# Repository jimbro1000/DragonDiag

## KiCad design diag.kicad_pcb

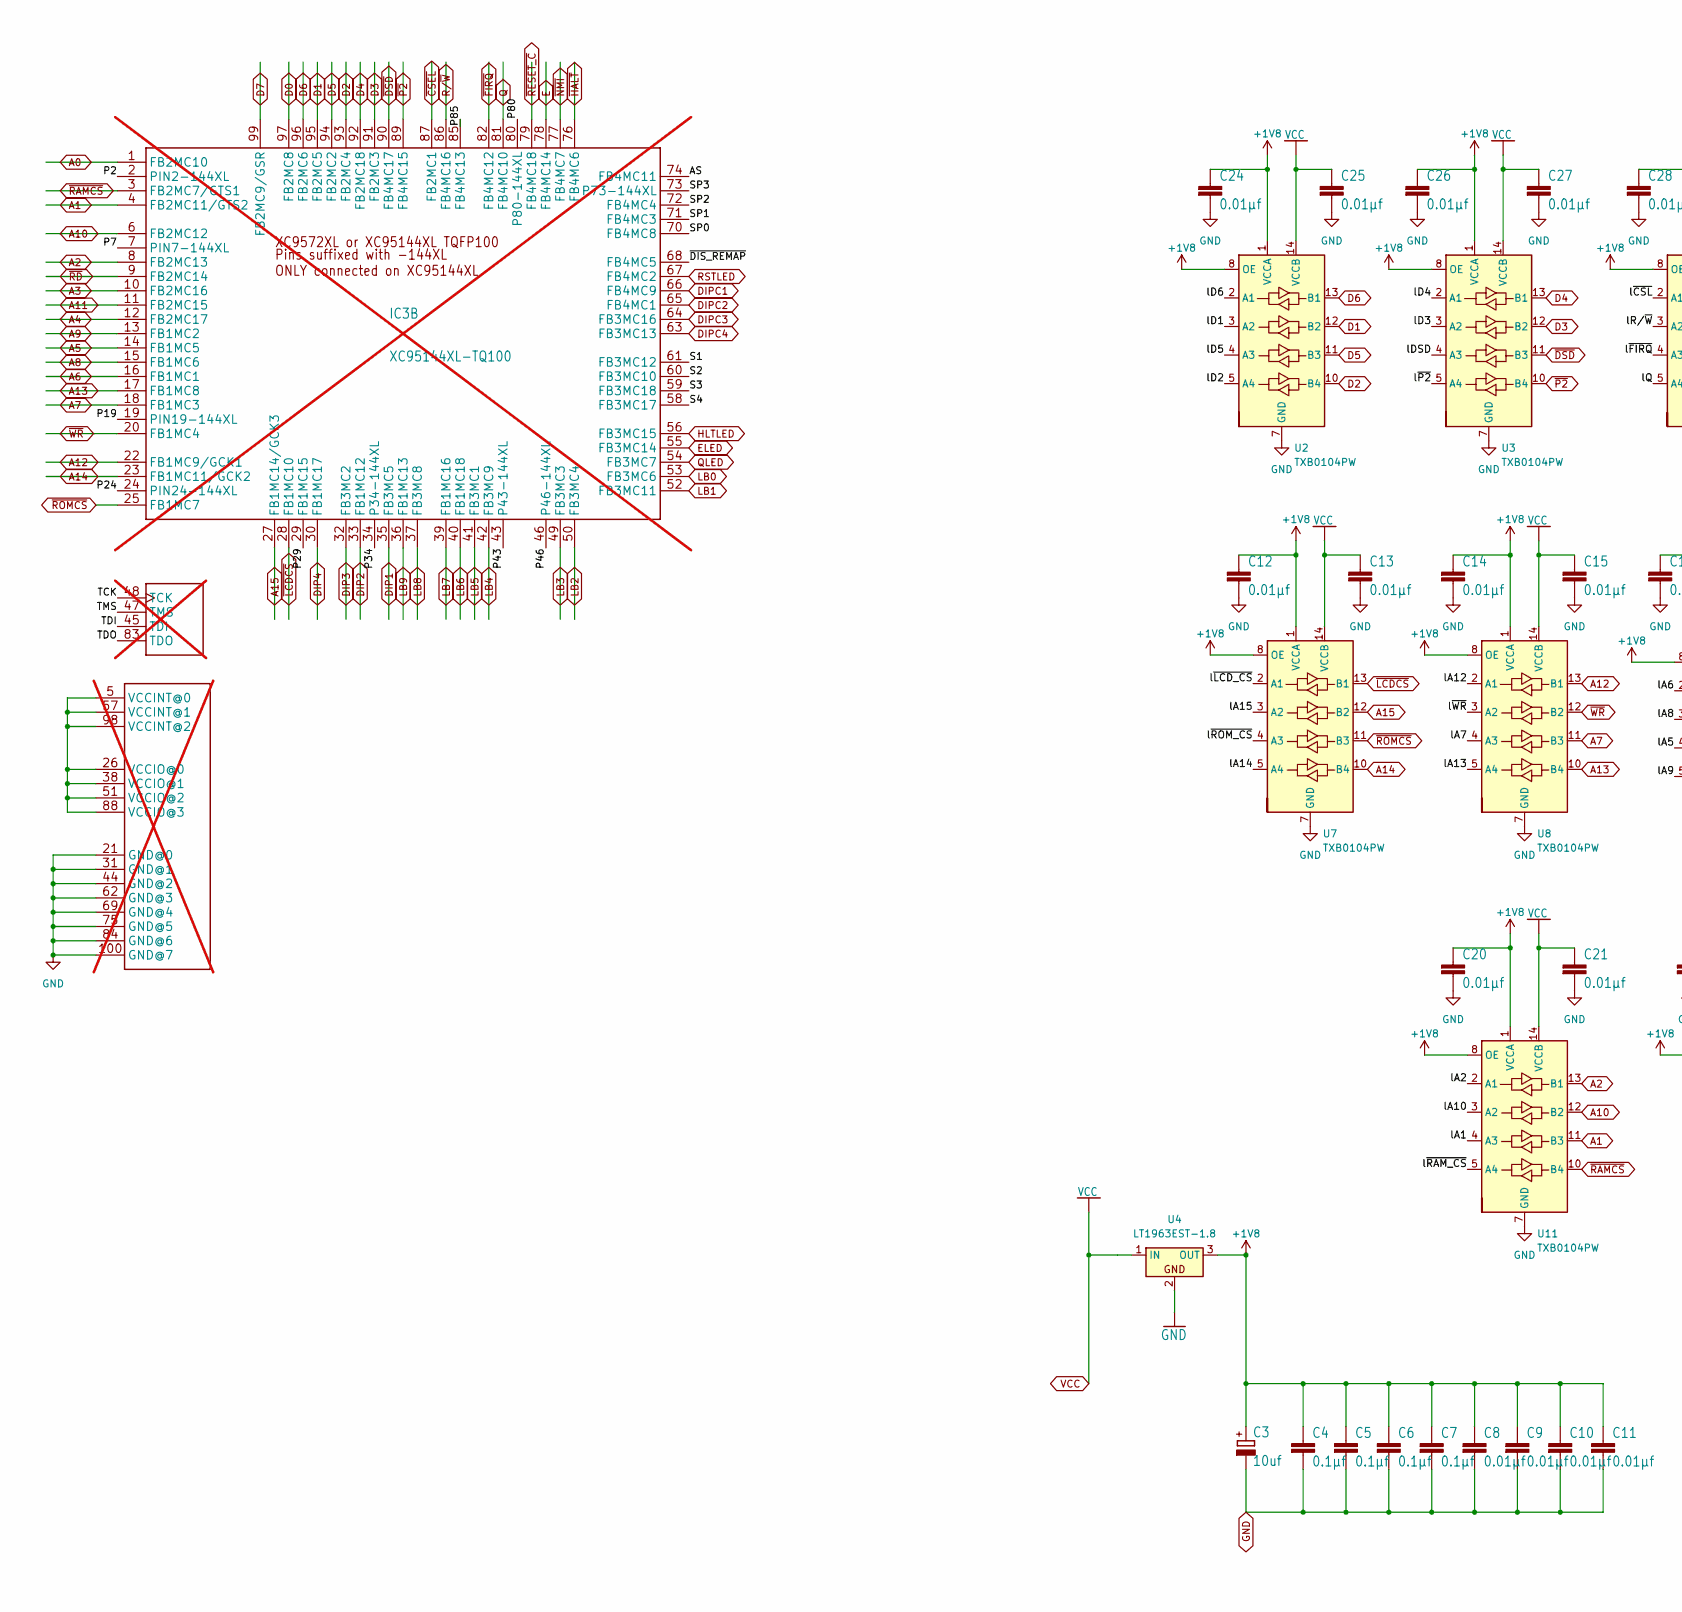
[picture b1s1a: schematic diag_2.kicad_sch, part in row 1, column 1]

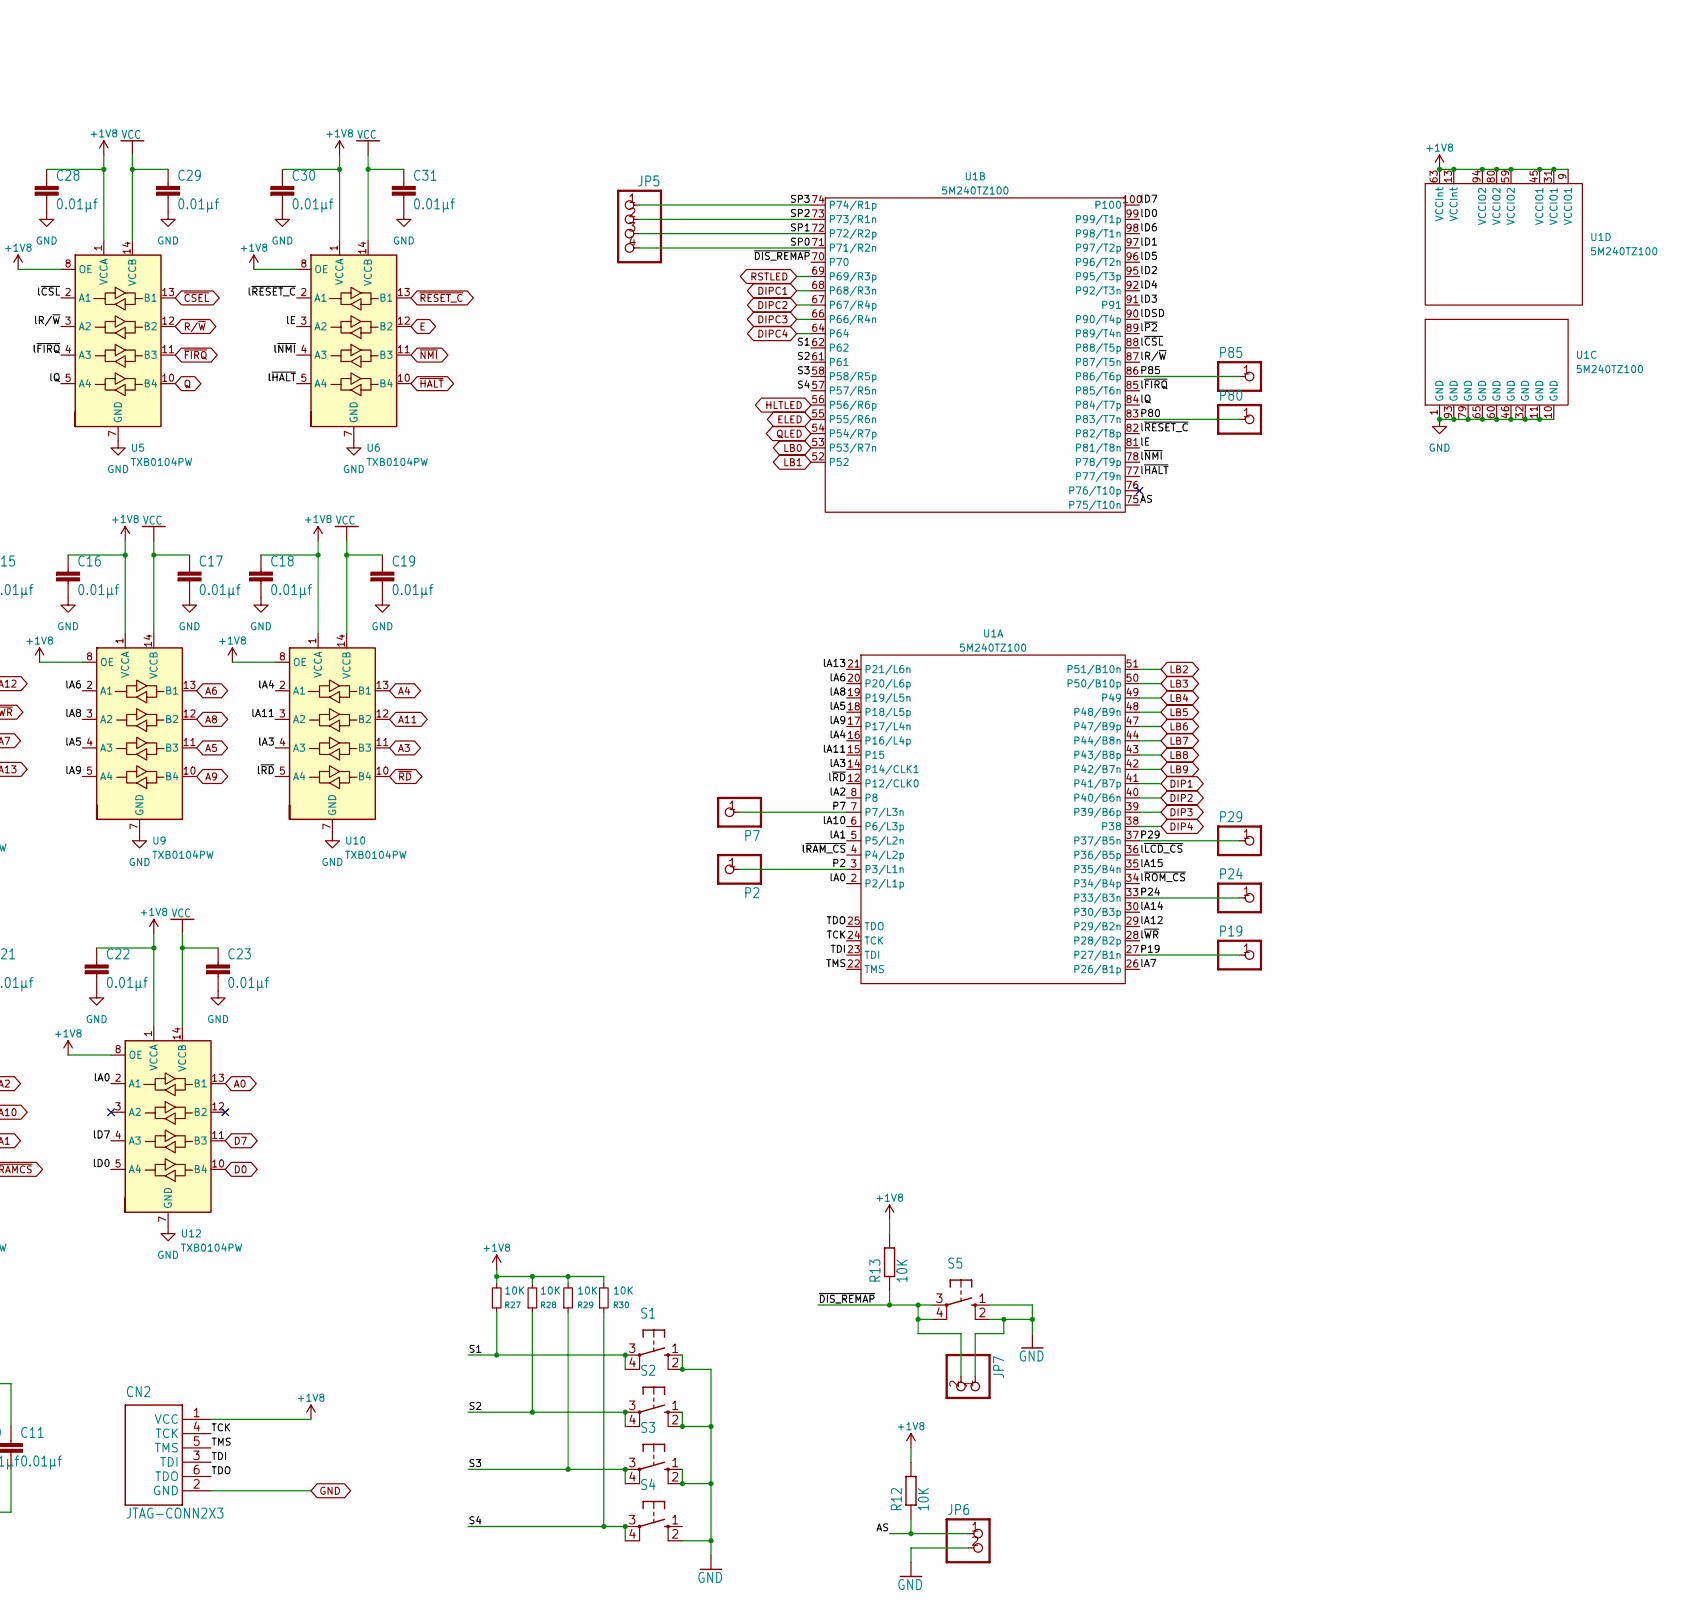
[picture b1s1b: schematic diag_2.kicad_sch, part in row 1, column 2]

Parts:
C3: 10uf; TT2D7
C4, C5, C6, C7: 0.1µf; C_0603_1608Metric
C8, C9, C10, C11, C12, C13, C14, C15, C16, C17, C18, C19, C20, C21, C22, C23, C24, C25, C26, C27, C28, C29, C30, C31: 0.01µf; C_0603_1608Metric
CN2: JTAG-CONN2X3; 2X3
IC3: XC95144XL-TQ100; TQ100; not fitted
JP5: PINHD-1X4; 1X04
JP6, JP7: PINHD-1X2; 1X02
P2, P7, P19, P24, P29, P80, P85: PINHD-1X1; 1X01
R12, R13, R27, R28, R29, R30: 10K; R_0805_2012Metric
S1, S2, S3, S4, S5: 10-XX; B3F-10XX
U1: 5M240TZ100; TQFP-100_14x14mm_P0.5mm
U2, U3, U5, U6, U7, U8, U9, U10, U11, U12: TXB0104PW; TSSOP-14_4.4x5mm_P0.65mm
U4: LT1963EST-1.8; SOT-223-3_TabPin2

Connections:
+1V8: C3.+, C4.1, C5.1, C6.1, C7.1, C8.1, C9.1, C10.1, C11.1, C12.1, C14.1, C16.1, C18.1, C20.1, C22.1, C24.1, C26.1, C28.1, C30.1, CN2.1 (VCC), R12.2, R13.2, R27.2, R28.2, R29.2, R30.2, U1.9 (VCCIO1), U1.13 (VCCInt), U1.31 (VCCIO1), U1.45 (VCCIO1), U1.59 (VCCIO2), U1.63 (VCCInt), U1.80 (VCCIO2), U1.94 (VCCIO2), U2.1 (VCCA), U2.8 (OE), U3.1 (VCCA), U3.8 (OE), U4.3 (OUT), U5.1 (VCCA), U5.8 (OE), U6.1 (VCCA), U6.8 (OE), U7.1 (VCCA), U7.8 (OE), U8.1 (VCCA), U8.8 (OE), U9.1 (VCCA), U9.8 (OE), U10.1 (VCCA), U10.8 (OE), U11.1 (VCCA), U11.8 (OE), U12.1 (VCCA), U12.8 (OE); also elsewhere on the board
/diag_2/AS: IC3.74 (FB4MC11), JP6.1, R12.1, U1.75 (P75/T10n)
/diag_2/P2: IC3.2 (PIN2-144XL), P2.1, U1.3 (P3/L1n)
/diag_2/P7: IC3.7 (PIN7-144XL), P7.1, U1.7 (P7/L3n)
/diag_2/P19: IC3.19 (PIN19-144XL), P19.1, U1.27 (P27/B1n)
/diag_2/P24: IC3.24 (PIN24-144XL), P24.1, U1.33 (P33/B3n)
/diag_2/P29: IC3.29 (FB1MC15), P29.1, U1.37 (P37/B5n)
/diag_2/P80: IC3.80 (P80-144XL), P80.1, U1.83 (P83/T7n)
/diag_2/P85: IC3.85 (FB4MC13), P85.1, U1.86 (P86/T6p)
/diag_2/S1: IC3.61 (FB3MC12), R27.1, S1.3, S1.4 (P1), U1.62
/diag_2/S2: IC3.60 (FB3MC10), R28.1, S2.3, S2.4 (P1), U1.61
/diag_2/S3: IC3.59 (FB3MC18), R29.1, S3.3, S3.4 (P1), U1.58 (P58/R5p)
/diag_2/S4: IC3.58 (FB3MC17), R30.1, S4.3, S4.4 (P1), U1.57 (P57/R5n)
/diag_2/SP0: IC3.70 (FB4MC8), JP5.4, U1.71 (P71/R2n)
/diag_2/SP1: IC3.71 (FB4MC3), JP5.3, U1.72 (P72/R2p)
/diag_2/SP2: IC3.72 (FB4MC4), JP5.2, U1.73 (P73/R1n)
/diag_2/SP3: IC3.73 (P73-144XL), JP5.1, U1.74 (P74/R1p)
/diag_2/TCK: CN2.4 (TCK), IC3.48 (TCK), U1.24 (TCK)
/diag_2/TDI: CN2.3 (TDI), IC3.45 (TDI), U1.23 (TDI)
/diag_2/TDO: CN2.6 (TDO), IC3.83 (TDO), U1.25 (TDO)
/diag_2/TMS: CN2.5 (TMS), IC3.47 (TMS), U1.22 (TMS)
/diag_2/lA0: U1.2 (P2/L1p), U12.2 (A1)
/diag_2/lA1: U1.5 (P5/L2n), U11.4 (A3)
/diag_2/lA2: U1.8, U11.2 (A1)
/diag_2/lA3: U1.14 (P14/CLK1), U10.4 (A3)
/diag_2/lA4: U1.16 (P16/L4p), U10.2 (A1)
/diag_2/lA5: U1.18 (P18/L5p), U9.4 (A3)
/diag_2/lA6: U1.20 (P20/L6p), U9.2 (A1)
/diag_2/lA7: U1.26 (P26/B1p), U8.4 (A3)
/diag_2/lA8: U1.19 (P19/L5n), U9.3 (A2)
/diag_2/lA9: U1.17 (P17/L4n), U9.5 (A4)
/diag_2/lA10: U1.6 (P6/L3p), U11.3 (A2)
/diag_2/lA11: U1.15, U10.3 (A2)
/diag_2/lA12: U1.29 (P29/B2n), U8.2 (A1)
/diag_2/lA13: U1.21 (P21/L6n), U8.5 (A4)
/diag_2/lA14: U1.30 (P30/B3p), U7.5 (A4)
/diag_2/lA15: U1.35 (P35/B4n), U7.3 (A2)
/diag_2/lD0: U1.99 (P99/T1p), U12.5 (A4)
/diag_2/lD1: U1.97 (P97/T2p), U2.3 (A2)
/diag_2/lD2: U1.95 (P95/T3p), U2.5 (A4)
/diag_2/lD3: U1.91, U3.3 (A2)
/diag_2/lD4: U1.92 (P92/T3n), U3.2 (A1)
/diag_2/lD5: U1.96 (P96/T2n), U2.4 (A3)
/diag_2/lD6: U1.98 (P98/T1n), U2.2 (A1)
/diag_2/lD7: U1.100, U12.4 (A3)
/diag_2/lDSD: U1.90 (P90/T4p), U3.4 (A3)
/diag_2/lE: U1.81 (P81/T8n), U6.3 (A2)
/diag_2/lQ: U1.84 (P84/T7p), U5.5 (A4)
/diag_2/lR/~W: U1.87 (P87/T5n), U5.3 (A2)
/diag_2/l~CSL: U1.88 (P88/T5p), U5.2 (A1)
/diag_2/l~FIRQ: U1.85 (P85/T6n), U5.4 (A3)
/diag_2/l~HALT: U1.77 (P77/T9n), U6.5 (A4)
/diag_2/l~LCD_CS: U1.36 (P36/B5p), U7.2 (A1)
/diag_2/l~NMI: U1.78 (P78/T9p), U6.4 (A3)
/diag_2/l~P2: U1.89 (P89/T4n), U3.5 (A4)
/diag_2/l~RAM_CS: U1.4 (P4/L2p), U11.5 (A4)
/diag_2/l~RD: U1.12 (P12/CLK0), U10.5 (A4)
/diag_2/l~RESET_C: U1.82 (P82/T8p), U6.2 (A1)
/diag_2/l~ROM_CS: U1.34 (P34/B4p), U7.4 (A3)
/diag_2/l~WR: U1.28 (P28/B2p), U8.3 (A2)
/diag_2/~DIS_REMAP: IC3.68 (FB4MC5), JP7.2, R13.1, S5.3, S5.4 (P1), U1.70
A0: IC3.1 (FB2MC10), U12.13 (B1); also elsewhere on the board
A1: IC3.4 (FB2MC11/GTS2), U11.11 (B3); also elsewhere on the board
A2: IC3.8 (FB2MC13), U11.13 (B1); also elsewhere on the board
A3: IC3.10 (FB2MC16), U10.11 (B3); also elsewhere on the board
A4: IC3.12 (FB2MC17), U10.13 (B1); also elsewhere on the board
A5: IC3.14 (FB1MC5), U9.11 (B3); also elsewhere on the board
A6: IC3.16 (FB1MC1), U9.13 (B1); also elsewhere on the board
A7: IC3.18 (FB1MC3), U8.11 (B3); also elsewhere on the board
A8: IC3.15 (FB1MC6), U9.12 (B2); also elsewhere on the board
A9: IC3.13 (FB1MC2), U9.10 (B4); also elsewhere on the board
A10: IC3.6 (FB2MC12), U11.12 (B2); also elsewhere on the board
A11: IC3.11 (FB2MC15), U10.12 (B2); also elsewhere on the board
A12: IC3.22 (FB1MC9/GCK1), U8.13 (B1); also elsewhere on the board
A13: IC3.17 (FB1MC8), U8.10 (B4); also elsewhere on the board
A14: IC3.23 (FB1MC11/GCK2), U7.10 (B4); also elsewhere on the board
A15: IC3.27 (FB1MC14/GCK3), U7.12 (B2); also elsewhere on the board
D0: IC3.97 (FB2MC8), U12.10 (B4); also elsewhere on the board
D1: IC3.95 (FB2MC5), U2.12 (B2); also elsewhere on the board
D2: IC3.93 (FB2MC4), U2.10 (B4); also elsewhere on the board
D3: IC3.91 (FB2MC3), U3.12 (B2); also elsewhere on the board
D4: IC3.92 (FB2MC18), U3.13 (B1); also elsewhere on the board
D5: IC3.94 (FB2MC2), U2.11 (B3); also elsewhere on the board
D6: IC3.96 (FB2MC6), U2.13 (B1); also elsewhere on the board
D7: IC3.99 (FB2MC9/GSR), U12.11 (B3); also elsewhere on the board
DIP1: IC3.35 (FB3MC5), U1.41 (P41/B7p); also elsewhere on the board
DIP2: IC3.33 (FB1MC12), U1.40 (P40/B6n); also elsewhere on the board
DIP3: IC3.32 (FB3MC2), U1.39 (P39/B6p); also elsewhere on the board
DIP4: IC3.30 (FB1MC17), U1.38; also elsewhere on the board
DIPC1: IC3.66 (FB4MC9), U1.68 (P68/R3n); also elsewhere on the board
DIPC2: IC3.65 (FB4MC1), U1.67 (P67/R4p); also elsewhere on the board
DIPC3: IC3.64 (FB3MC16), U1.66 (P66/R4n); also elsewhere on the board
DIPC4: IC3.63 (FB3MC13), U1.64; also elsewhere on the board
E: IC3.78 (FB4MC14), U6.12 (B2); also elsewhere on the board
ELED: IC3.55 (FB3MC14), U1.55 (P55/R6n); also elsewhere on the board
GND: C3.-, C4.2, C5.2, C6.2, C7.2, C8.2, C9.2, C10.2, C11.2, C12.2, C13.2, C14.2, C15.2, C16.2, C17.2, C18.2, C19.2, C20.2, C21.2, C22.2, C23.2, C24.2, C25.2, C26.2, C27.2, C28.2, C29.2, C30.2, C31.2, CN2.2 (GND), IC3.21 (GND@0), IC3.31 (GND@1), IC3.44 (GND@2), IC3.62 (GND@3), IC3.69 (GND@4), IC3.75 (GND@5), IC3.84 (GND@6), IC3.100 (GND@7), JP6.2, JP7.1, S1.1 (S), S1.2 (S1), S2.1 (S), S2.2 (S1), S3.1 (S), S3.2 (S1), S4.2 (S1), S5.1 (S), S5.2 (S1), U1.1 (GND), U1.10 (GND), U1.11 (GND), U1.32 (GND), U1.46 (GND), U1.60 (GND), U1.65 (GND), U1.79 (GND), U1.93 (GND), U2.7 (GND), U3.7 (GND), U4.2, U5.7 (GND), U6.7 (GND), U7.7 (GND), U8.7 (GND), U9.7 (GND), U10.7 (GND), U11.7 (GND), U12.7 (GND); also elsewhere on the board
HLTLED: IC3.56 (FB3MC15), U1.56 (P56/R6p); also elsewhere on the board
LB0: IC3.53 (FB3MC6), U1.53 (P53/R7n); also elsewhere on the board
LB1: IC3.52 (FB3MC11), U1.52; also elsewhere on the board
LB2: IC3.50 (FB3MC4), U1.51 (P51/B10n); also elsewhere on the board
LB3: IC3.49 (FB3MC3), U1.50 (P50/B10p); also elsewhere on the board
LB4: IC3.42 (FB3MC9), U1.49; also elsewhere on the board
LB5: IC3.41 (FB3MC1), U1.48 (P48/B9n); also elsewhere on the board
LB6: IC3.40 (FB1MC18), U1.47 (P47/B9p); also elsewhere on the board
LB7: IC3.39 (FB1MC16), U1.44 (P44/B8n); also elsewhere on the board
LB8: IC3.37 (FB3MC8), U1.43 (P43/B8p); also elsewhere on the board
LB9: IC3.36 (FB1MC13), U1.42 (P42/B7n); also elsewhere on the board
unnamed: IC3.5 (VCCINT@0), IC3.26 (VCCIO@0), IC3.38 (VCCIO@1), IC3.51 (VCCIO@2), IC3.57 (VCCINT@1), IC3.88 (VCCIO@3), IC3.98 (VCCINT@2)
Q: IC3.81 (FB4MC10), U5.10 (B4); also elsewhere on the board
QLED: IC3.54 (FB3MC7), U1.54 (P54/R7p); also elsewhere on the board
RSTLED: IC3.67 (FB4MC2), U1.69 (P69/R3p); also elsewhere on the board
R/~W: IC3.86 (FB4MC16), U5.12 (B2); also elsewhere on the board
VCC: C13.1, C15.1, C17.1, C19.1, C21.1, C23.1, C25.1, C27.1, C29.1, C31.1, U2.14 (VCCB), U3.14 (VCCB), U4.1 (IN), U5.14 (VCCB), U6.14 (VCCB), U7.14 (VCCB), U8.14 (VCCB), U9.14 (VCCB), U10.14 (VCCB), U11.14 (VCCB), U12.14 (VCCB); also elsewhere on the board
~CSEL: IC3.87 (FB2MC1), U5.13 (B1); also elsewhere on the board
~DSD: IC3.90 (FB4MC17), U3.11 (B3); also elsewhere on the board
~FIRQ: IC3.82 (FB4MC12), U5.11 (B3); also elsewhere on the board
~HALT: IC3.76 (FB4MC6), U6.10 (B4); also elsewhere on the board
~LCDCS: IC3.28 (FB1MC10), U7.13 (B1); also elsewhere on the board
~NMI: IC3.77 (FB4MC7), U6.11 (B3); also elsewhere on the board
~P2: IC3.89 (FB4MC15), U3.10 (B4); also elsewhere on the board
~RAMCS: IC3.3 (FB2MC7/GTS1), U11.10 (B4); also elsewhere on the board
~RD: IC3.9 (FB2MC14), U10.10 (B4); also elsewhere on the board
~RESET_C: IC3.79 (FB4MC18), U6.13 (B1); also elsewhere on the board
~ROMCS: IC3.25 (FB1MC7), U7.11 (B3); also elsewhere on the board
~WR: IC3.20 (FB1MC4), U8.12 (B2); also elsewhere on the board

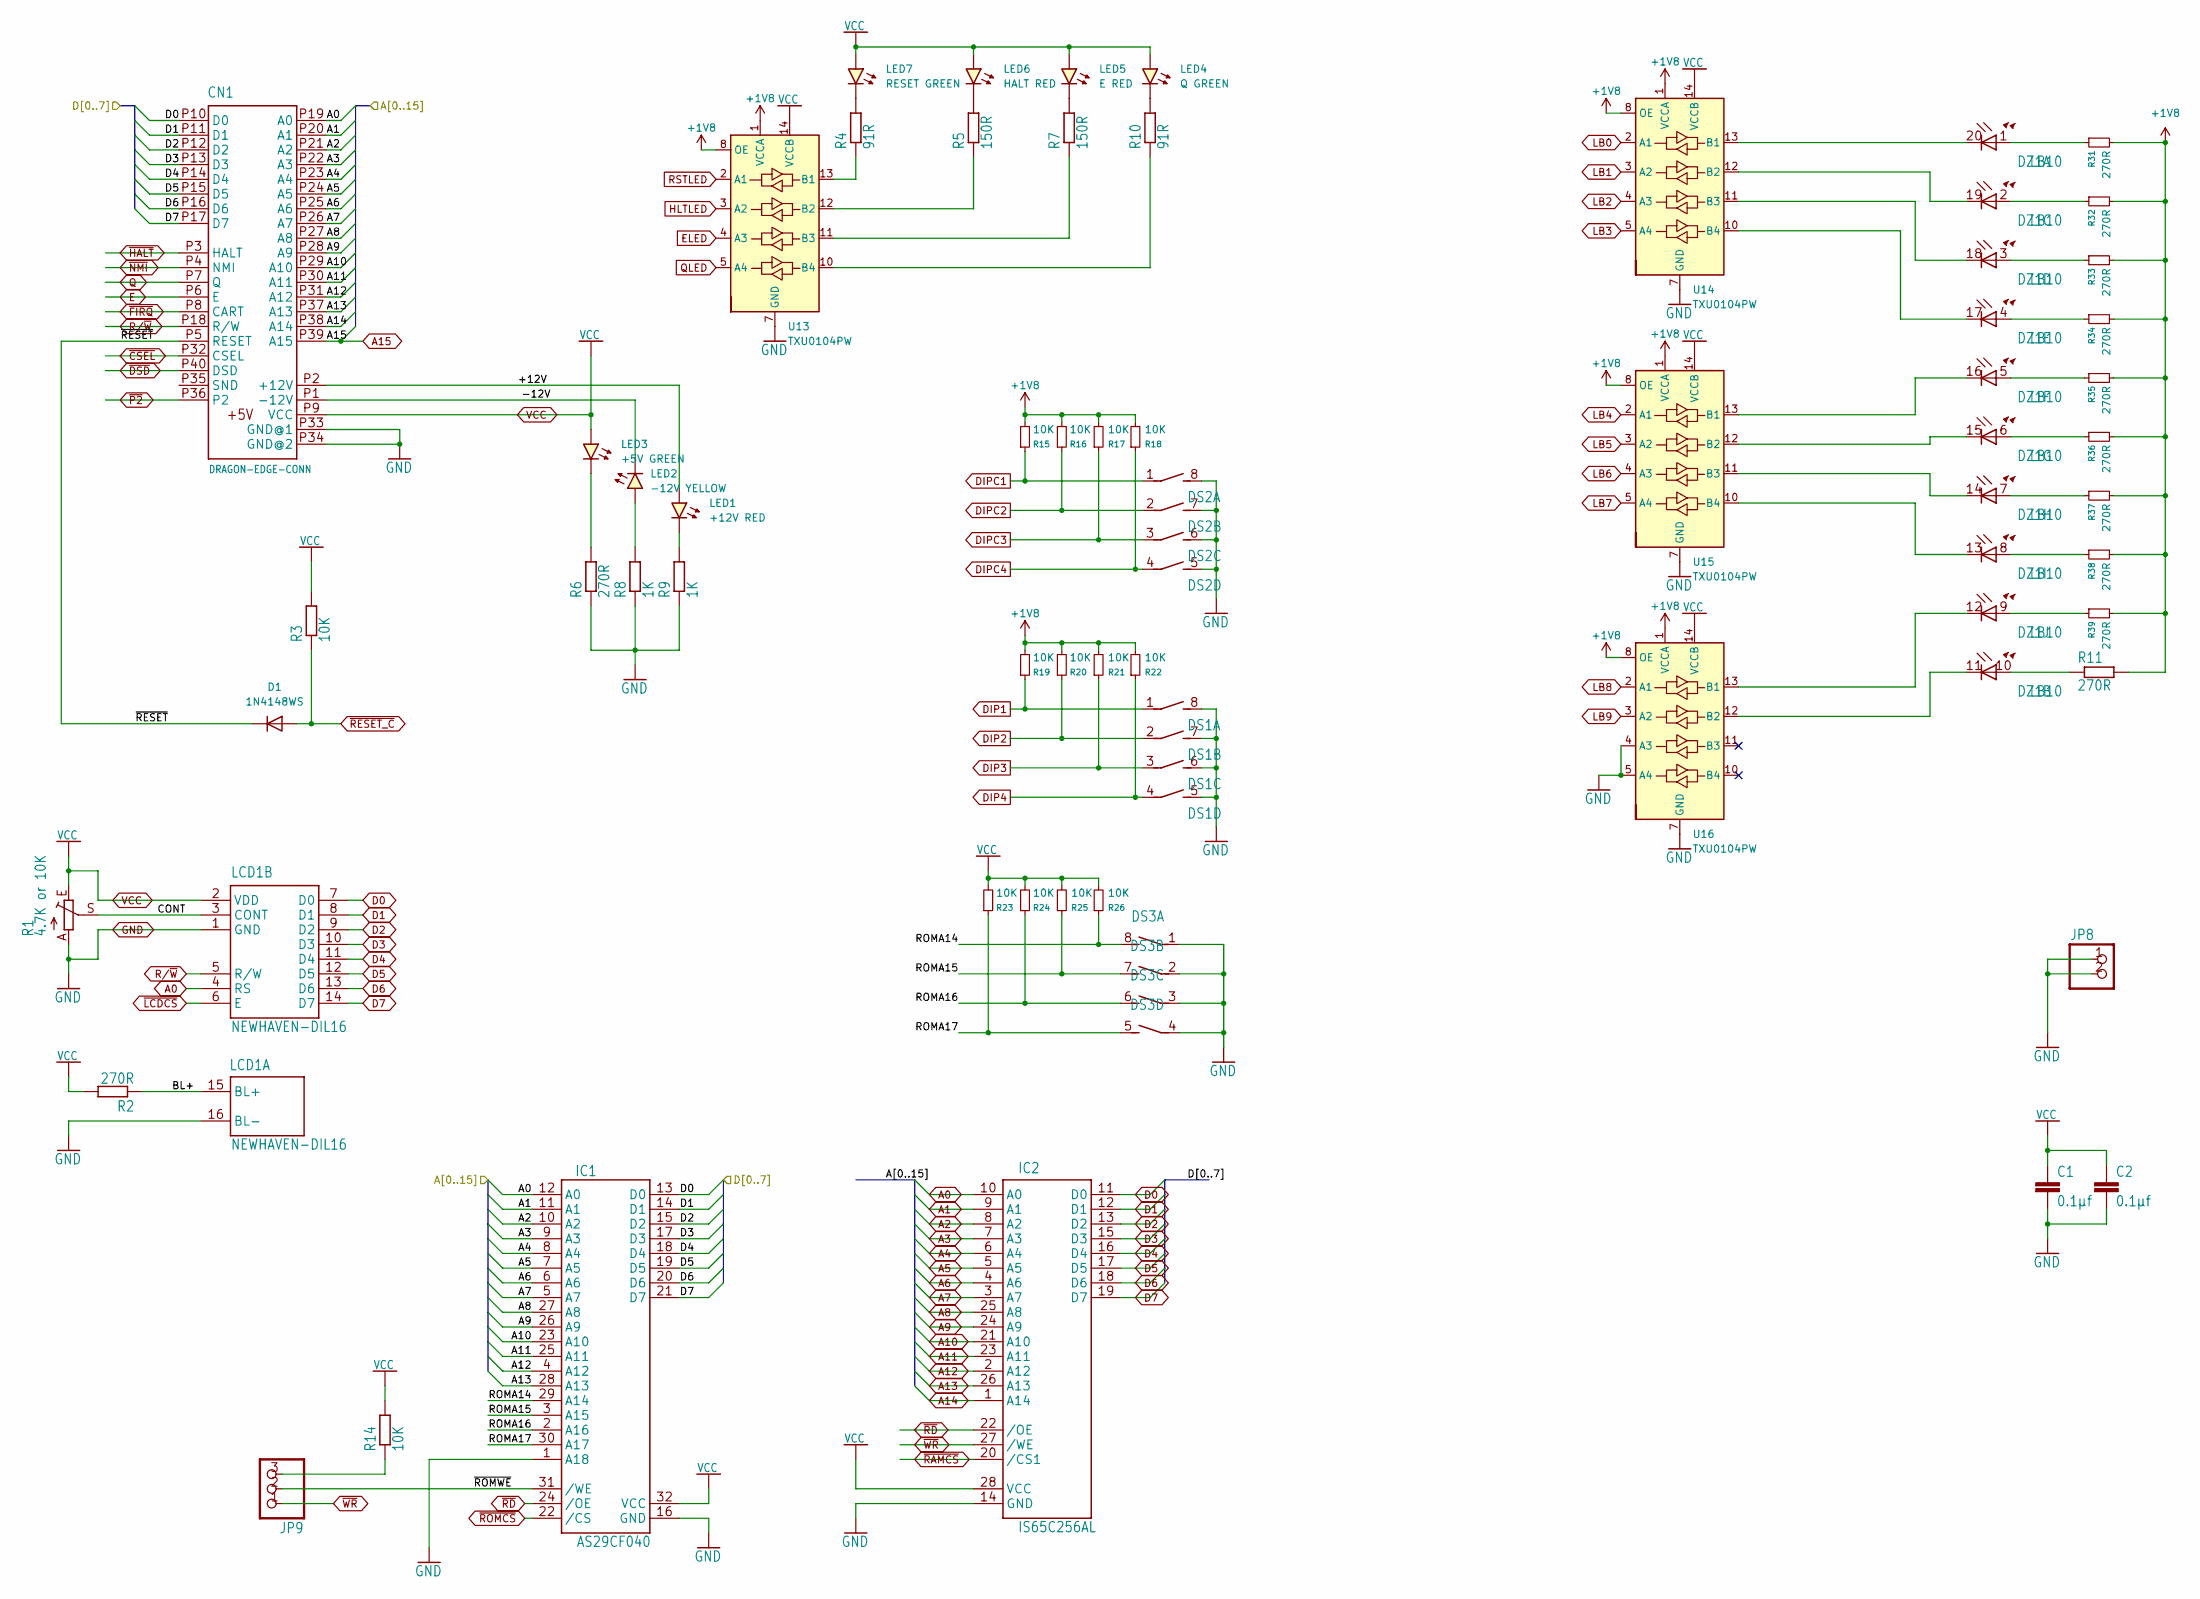
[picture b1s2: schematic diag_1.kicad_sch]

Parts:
C1, C2: 0.1µf; C_0805_2012Metric
CN1: DRAGON-EDGE-CONN; EDGE-40-01
D1: 1N4148WS; D_SOD-323
DS1, DS2, DS3: DIP04S
DZ1: LB10
IC1: AS29CF040; PLCC-32_THT-Socket
IC2: IS65C256AL; SOP-28_8.4x18.16mm_P1.27mm; DigiKey 706-1043-ND
JP8: PINHD-1X2; 1X02
JP9: PINHD-1X3; 1X03
LCD1: NEWHAVEN-DIL16; 2X08
LED1: +12V RED; LED_0805_2012Metric
LED2: -12V YELLOW; LED_0805_2012Metric
LED3: +5V GREEN; LED_0805_2012Metric
LED4: Q GREEN; LED_0603_1608Metric; LCSC C965804
LED5: E RED; LED_0603_1608Metric; LCSC C965799
LED6: HALT RED; LED_0603_1608Metric; LCSC C965799
LED7: RESET GREEN; LED_0603_1608Metric; LCSC C965804
R1: 4.7K or 10K; CA9V
R2, R6, R11, R31, R32, R33, R34, R35, R36, R37, R38, R39: 270R; R_0805_2012Metric
R3, R14, R15, R16, R17, R18, R19, R20, R21, R22, R23, R24, R25, R26: 10K; R_0805_2012Metric
R4, R10: 91R; R_0805_2012Metric
R5, R7: 150R; R_0805_2012Metric
R8, R9: 1K; R_0805_2012Metric
U13, U14, U15, U16: TXU0104PW; TSSOP-14_4.4x5mm_P0.65mm

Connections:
+1V8: R11.2, R15.2, R16.2, R17.2, R18.2, R19.2, R20.2, R21.2, R22.2, R31.2, R32.2, R33.2, R34.2, R35.2, R36.2, R37.2, R38.2, R39.2, U13.1 (VCCA), U13.8 (OE), U14.1 (VCCA), U14.8 (OE), U15.1 (VCCA), U15.8 (OE), U16.1 (VCCA), U16.8 (OE); also elsewhere on the board
/diag_1/+12V: CN1.P2 (+12V), LED1.2 (A)
/diag_1/-12V: CN1.P1 (-12V), LED2.1 (K)
/diag_1/BL+: LCD1.15 (BL+), R2.1
/diag_1/CONT: LCD1.3 (CONT), R1.S
/diag_1/ROMA14: DS3.8 (2), IC1.29 (A14), R26.1
/diag_1/ROMA15: DS3.7 (2), IC1.3 (A15), R25.1
/diag_1/ROMA16: DS3.6 (2), IC1.2 (A16), R24.1
/diag_1/ROMA17: DS3.5 (2), IC1.30 (A17), R23.1
/diag_1/~RESET: CN1.P5 (RESET), D1.1 (K)
/diag_1/~ROMWE: IC1.31 (/WE), JP9.2
A0: CN1.P19 (A0), IC1.12 (A0), IC2.10 (A0), LCD1.4 (RS); also elsewhere on the board
A1: CN1.P20 (A1), IC1.11 (A1), IC2.9 (A1); also elsewhere on the board
A2: CN1.P21 (A2), IC1.10 (A2), IC2.8 (A2); also elsewhere on the board
A3: CN1.P22 (A3), IC1.9 (A3), IC2.7 (A3); also elsewhere on the board
A4: CN1.P23 (A4), IC1.8 (A4), IC2.6 (A4); also elsewhere on the board
A5: CN1.P24 (A5), IC1.7 (A5), IC2.5 (A5); also elsewhere on the board
A6: CN1.P25 (A6), IC1.6 (A6), IC2.4 (A6); also elsewhere on the board
A7: CN1.P26 (A7), IC1.5 (A7), IC2.3 (A7); also elsewhere on the board
A8: CN1.P27 (A8), IC1.27 (A8), IC2.25 (A8); also elsewhere on the board
A9: CN1.P28 (A9), IC1.26 (A9), IC2.24 (A9); also elsewhere on the board
A10: CN1.P29 (A10), IC1.23 (A10), IC2.21 (A10); also elsewhere on the board
A11: CN1.P30 (A11), IC1.25 (A11), IC2.23 (A11); also elsewhere on the board
A12: CN1.P31 (A12), IC1.4 (A12), IC2.2 (A12); also elsewhere on the board
A13: CN1.P37 (A13), IC1.28 (A13), IC2.26 (A13); also elsewhere on the board
A14: CN1.P38 (A14), IC2.1 (A14); also elsewhere on the board
A15: CN1.P39 (A15); also elsewhere on the board
D0: CN1.P10 (D0), IC1.13 (D0), IC2.11 (D0), LCD1.7 (D0); also elsewhere on the board
D1: CN1.P11 (D1), IC1.14 (D1), IC2.12 (D1), LCD1.8 (D1); also elsewhere on the board
D2: CN1.P12 (D2), IC1.15 (D2), IC2.13 (D2), LCD1.9 (D2); also elsewhere on the board
D3: CN1.P13 (D3), IC1.17 (D3), IC2.15 (D3), LCD1.10 (D3); also elsewhere on the board
D4: CN1.P14 (D4), IC1.18 (D4), IC2.16 (D4), LCD1.11 (D4); also elsewhere on the board
D5: CN1.P15 (D5), IC1.19 (D5), IC2.17 (D5), LCD1.12 (D5); also elsewhere on the board
D6: CN1.P16 (D6), IC1.20 (D6), IC2.18 (D6), LCD1.13 (D6); also elsewhere on the board
D7: CN1.P17 (D7), IC1.21 (D7), IC2.19 (D7), LCD1.14 (D7); also elsewhere on the board
DIP1: DS1.1, R19.1; also elsewhere on the board
DIP2: DS1.2 (1), R20.1; also elsewhere on the board
DIP3: DS1.3 (1), R21.1; also elsewhere on the board
DIP4: DS1.4 (1), R22.1; also elsewhere on the board
DIPC1: DS2.1, R15.1; also elsewhere on the board
DIPC2: DS2.2 (1), R16.1; also elsewhere on the board
DIPC3: DS2.3 (1), R17.1; also elsewhere on the board
DIPC4: DS2.4 (1), R18.1; also elsewhere on the board
E: CN1.P6 (E); also elsewhere on the board
ELED: U13.4 (A3); also elsewhere on the board
GND: C1.2, C2.2, CN1.P33 (GND@1), CN1.P34 (GND@2), DS1.5 (2), DS1.6 (2), DS1.7 (2), DS1.8 (2), DS2.5 (2), DS2.6 (2), DS2.7 (2), DS2.8 (2), DS3.1, DS3.2 (1), DS3.3 (1), DS3.4 (1), IC1.1 (A18), IC1.16 (GND), IC2.14 (GND), JP8.1, JP8.2, LCD1.1 (GND), LCD1.16 (BL-), R1.A, R6.1, R8.1, R9.1, U13.7 (GND), U14.7 (GND), U15.7 (GND), U16.4 (A3), U16.5 (A4), U16.7 (GND); also elsewhere on the board
HLTLED: U13.3 (A2); also elsewhere on the board
LB0: U14.2 (A1); also elsewhere on the board
LB1: U14.3 (A2); also elsewhere on the board
LB2: U14.4 (A3); also elsewhere on the board
LB3: U14.5 (A4); also elsewhere on the board
LB4: U15.2 (A1); also elsewhere on the board
LB5: U15.3 (A2); also elsewhere on the board
LB6: U15.4 (A3); also elsewhere on the board
LB7: U15.5 (A4); also elsewhere on the board
LB8: U16.2 (A1); also elsewhere on the board
LB9: U16.3 (A2); also elsewhere on the board
unnamed: DZ1.1 (A), R31.1
unnamed: DZ1.20 (C), U14.13 (B1)
unnamed: DZ1.10 (A), R11.1
unnamed: DZ1.11 (C), U16.12 (B2)
unnamed: DZ1.2 (A), R32.1
unnamed: DZ1.19 (C), U14.12 (B2)
unnamed: DZ1.3 (A), R33.1
unnamed: DZ1.18 (C), U14.11 (B3)
unnamed: DZ1.4 (A), R34.1
unnamed: DZ1.17 (C), U14.10 (B4)
unnamed: DZ1.5 (A), R35.1
unnamed: DZ1.16 (C), U15.13 (B1)
unnamed: DZ1.6 (A), R36.1
unnamed: DZ1.15 (C), U15.12 (B2)
unnamed: DZ1.7 (A), R37.1
unnamed: DZ1.14 (C), U15.11 (B3)
unnamed: DZ1.8 (A), R38.1
unnamed: DZ1.13 (C), U15.10 (B4)
unnamed: DZ1.9 (A), R39.1
unnamed: DZ1.12 (C), U16.13 (B1)
unnamed: JP9.3, R14.1
unnamed: LED1.1 (K), R9.2
unnamed: LED2.2 (A), R8.2
unnamed: LED3.1 (K), R6.2
unnamed: LED4.1 (K), R10.2
unnamed: LED5.1 (K), R7.2
unnamed: LED6.1 (K), R5.2
unnamed: LED7.1 (K), R4.2
unnamed: R4.1, U13.13 (B1)
unnamed: R5.1, U13.12 (B2)
unnamed: R7.1, U13.11 (B3)
unnamed: R10.1, U13.10 (B4)
Q: CN1.P7 (Q); also elsewhere on the board
QLED: U13.5 (A4); also elsewhere on the board
RSTLED: U13.2 (A1); also elsewhere on the board
R/~W: CN1.P18 (R/W), LCD1.5 (R/W); also elsewhere on the board
VCC: C1.1, C2.1, CN1.P9 (VCC), IC1.32 (VCC), IC2.28 (VCC), LCD1.2 (VDD), LED3.2 (A), LED4.2 (A), LED5.2 (A), LED6.2 (A), LED7.2 (A), R1.E, R2.2, R3.2, R14.2, R23.2, R24.2, R25.2, R26.2, U13.14 (VCCB), U14.14 (VCCB), U15.14 (VCCB), U16.14 (VCCB); also elsewhere on the board
~CSEL: CN1.P32 (CSEL); also elsewhere on the board
~DSD: CN1.P40 (DSD); also elsewhere on the board
~FIRQ: CN1.P8 (CART); also elsewhere on the board
~HALT: CN1.P3 (HALT); also elsewhere on the board
~LCDCS: LCD1.6 (E); also elsewhere on the board
~NMI: CN1.P4 (NMI); also elsewhere on the board
~P2: CN1.P36 (P2); also elsewhere on the board
~RAMCS: IC2.20 (/CS1); also elsewhere on the board
~RD: IC1.24 (/OE), IC2.22 (/OE); also elsewhere on the board
~RESET_C: D1.2 (A), R3.1; also elsewhere on the board
~ROMCS: IC1.22 (/CS); also elsewhere on the board
~WR: IC2.27 (/WE), JP9.1; also elsewhere on the board

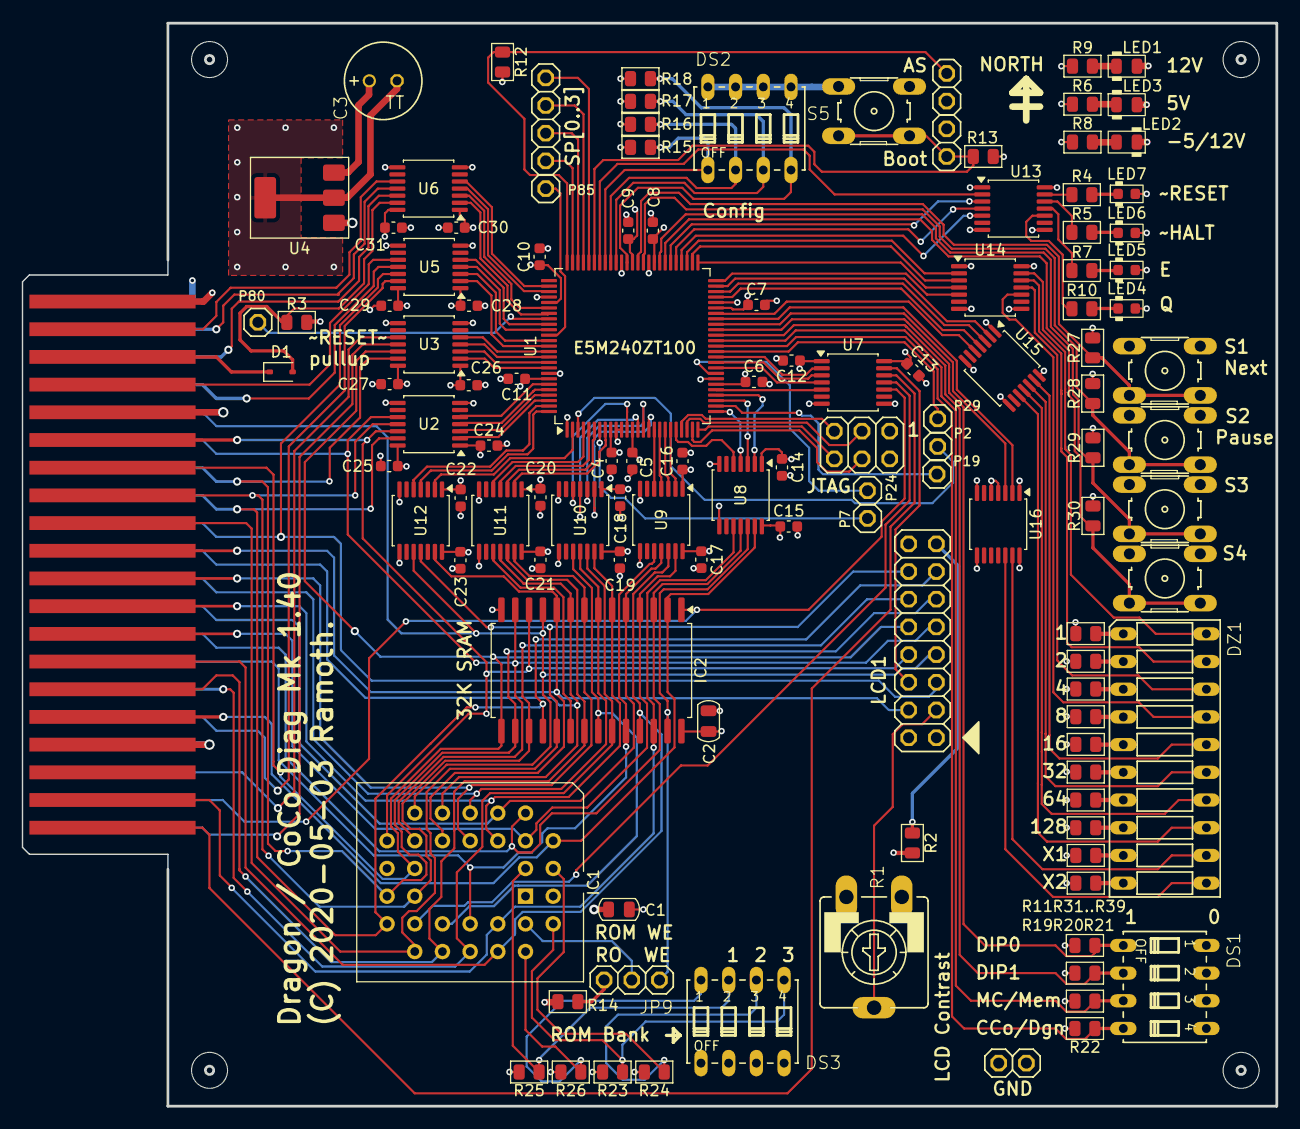
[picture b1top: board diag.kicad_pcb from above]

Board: 4 copper layers, 115.0 x 99.3 mm, 124 parts (0 on the bottom side), 166 nets.

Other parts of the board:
JP1, JP2, JP3, JP4: STAND-OFF

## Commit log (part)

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2025-05-21 start conversion to kicad

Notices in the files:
diag.kicad_pcb:
(C) 2020-05-03 Ramoth.
